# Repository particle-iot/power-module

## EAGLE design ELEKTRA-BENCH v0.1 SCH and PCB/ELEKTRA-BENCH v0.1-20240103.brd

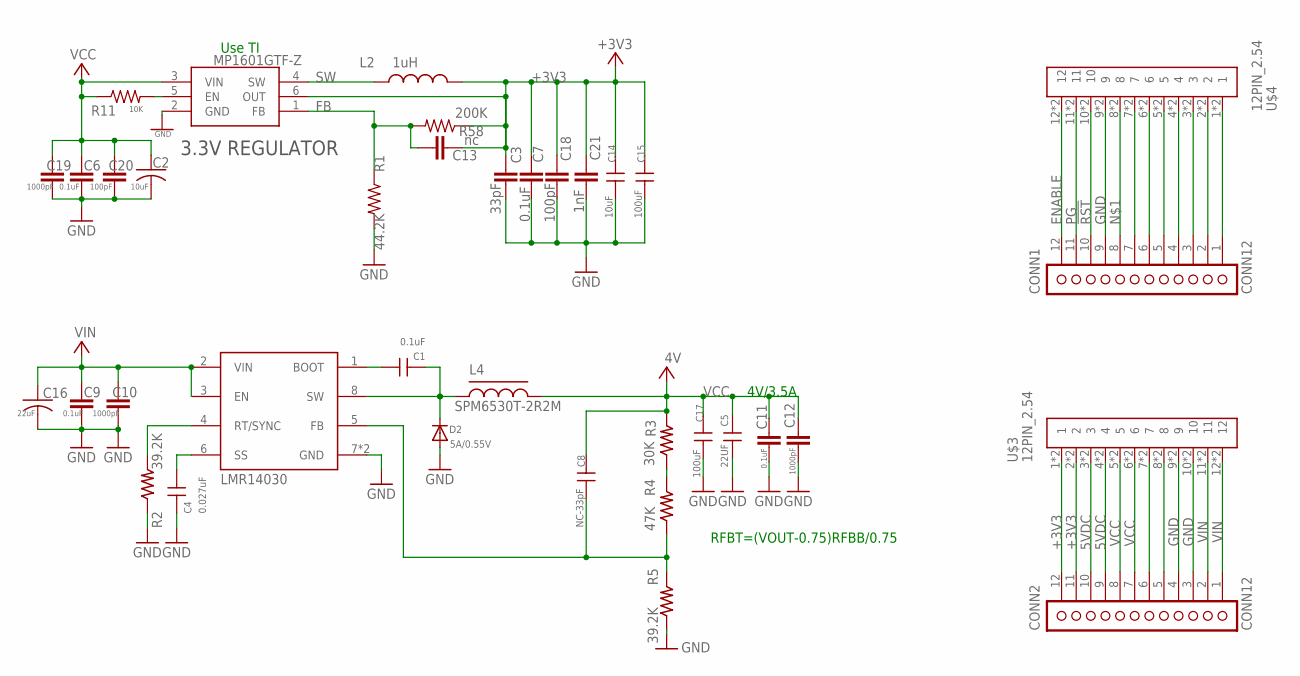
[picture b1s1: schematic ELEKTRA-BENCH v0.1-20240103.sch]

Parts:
C1: 0.1uF; C0402
C2: 10uF; C0603_B
C3: 33pF; C0402_B
C4: 0.027uF; C0402
C5: 22UF; C0805
C6, C7, C9, C11: 0.1uF; C0402_B
C8: NC-33pF; C0402
C10, C12, C19: 1000pF; C0402_B
C13: nc; C0402_B
C14: 10uF; C0805
C15, C17: 100uF; C1206
C16: 22uF; C0603_B
C18, C20: 100pF; C0402_B
C21: 1nF; C0402_B
CONN1, CONN2: CONN12; 1X12_SMD_STRAIGHT
D2: 5A/0.55V; SMADIODE
L2: 1uH; INDUCTOR-VLS-E
L4: SPM6530T-2R2M; INDCUTOR_SPM6530
R1: 44.2K; R0402_B
R2, R5: 39.2K; R-0402S
R3: 30K; R-0402S
R4: 47K; R-0402S
R11: 10K; R0402_B
R58: 200K; R0402_B
U2: LMR14030; SO_POWERPAD_8
U3: MP1601GTF-Z; SOTFL50P160X60-6N
U$3, U$4: 12PIN_2.54

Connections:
5VDC: CONN2.9, CONN2.10, U$3.3, U$3.4, U$3.P$3 (3), U$3.P$4 (4)
!RST: CONN1.10, U$4.10, U$4.P$10 (10)
+3V3: C3.2, C7.2, C13.1, C14.1, C15.1, C18.2, C21.2, CONN2.11, CONN2.12, L2.P$2 (2), R58.1, U3.6 (OUT), U$3.1, U$3.2, U$3.P$1 (1), U$3.P$2 (2)
ENABLE: CONN1.12, U$4.12, U$4.P$12 (12)
FB: C13.2, R1.1, R58.2, U3.1 (FB)
GND: C2.2, C3.1, C4.2, C5.2, C6.1, C7.1, C9.1, C10.1, C11.1, C12.1, C14.2, C15.2, C16.2, C17.2, C18.1, C19.1, C20.1, C21.1, CONN1.9, CONN2.3, CONN2.4, D2.A, R1.2, R2.1, R5.1, U2.7 (GND), U2.EP (GND), U3.2 (GND), U$3.9, U$3.10, U$3.P$9 (9), U$3.P$10 (10), U$4.9, U$4.P$9 (9)
unnamed: CONN1.8, U$4.8, U$4.P$8 (8)
unnamed: C8.1, R4.1, R5.2, U2.5 (FB)
unnamed: CONN1.7, U$4.7, U$4.P$7 (7)
unnamed: CONN1.6, U$4.6, U$4.P$6 (6)
unnamed: CONN1.5, U$4.5, U$4.P$5 (5)
unnamed: CONN1.4, U$4.4, U$4.P$4 (4)
unnamed: R11.2, U3.5 (EN)
unnamed: C4.1, U2.6 (SS)
unnamed: C1.2, D2.C, L4.1, U2.8 (SW)
unnamed: C1.1, U2.1 (BOOT)
unnamed: R2.2, U2.4 (RT/SYNC)
unnamed: R3.1, R4.2
unnamed: CONN1.3, U$4.3, U$4.P$3 (3)
unnamed: CONN1.2, U$4.2, U$4.P$2 (2)
unnamed: CONN1.1, U$4.1, U$4.P$1 (1)
unnamed: CONN2.6, U$3.7, U$3.P$7 (7)
unnamed: CONN2.5, U$3.8, U$3.P$8 (8)
PG: CONN1.11, U$4.11, U$4.P$11 (11)
SW: L2.P$1 (1), U3.4 (SW)
VCC: C2.1, C5.1, C6.2, C8.2, C11.2, C12.2, C17.1, C19.2, C20.2, CONN2.7, CONN2.8, L4.2, R3.2, R11.1, U3.3 (VIN), U$3.5, U$3.6, U$3.P$5 (5), U$3.P$6 (6)
VIN: C9.2, C10.2, C16.1, CONN2.1, CONN2.2, U2.2 (VIN), U2.3 (EN), U$3.11, U$3.12, U$3.P$11 (11), U$3.P$12 (12)

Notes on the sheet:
4V/3.5A
3.3V REGULATOR
RFBT=(VOUT-0.75)RFBB/0.75
Use TI

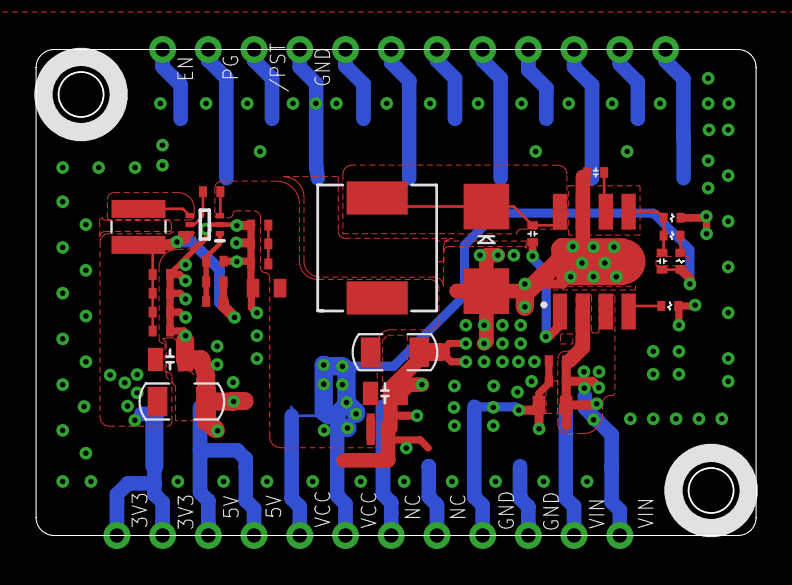
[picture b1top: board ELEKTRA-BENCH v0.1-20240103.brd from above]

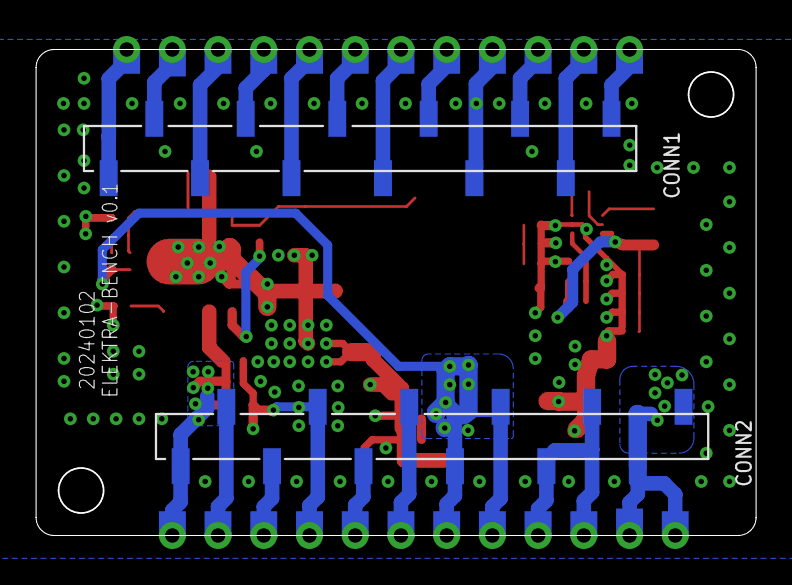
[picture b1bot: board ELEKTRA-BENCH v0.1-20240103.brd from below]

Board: 2 copper layers, 40.0 x 27.0 mm, 37 parts (2 on the bottom side), 27 nets.

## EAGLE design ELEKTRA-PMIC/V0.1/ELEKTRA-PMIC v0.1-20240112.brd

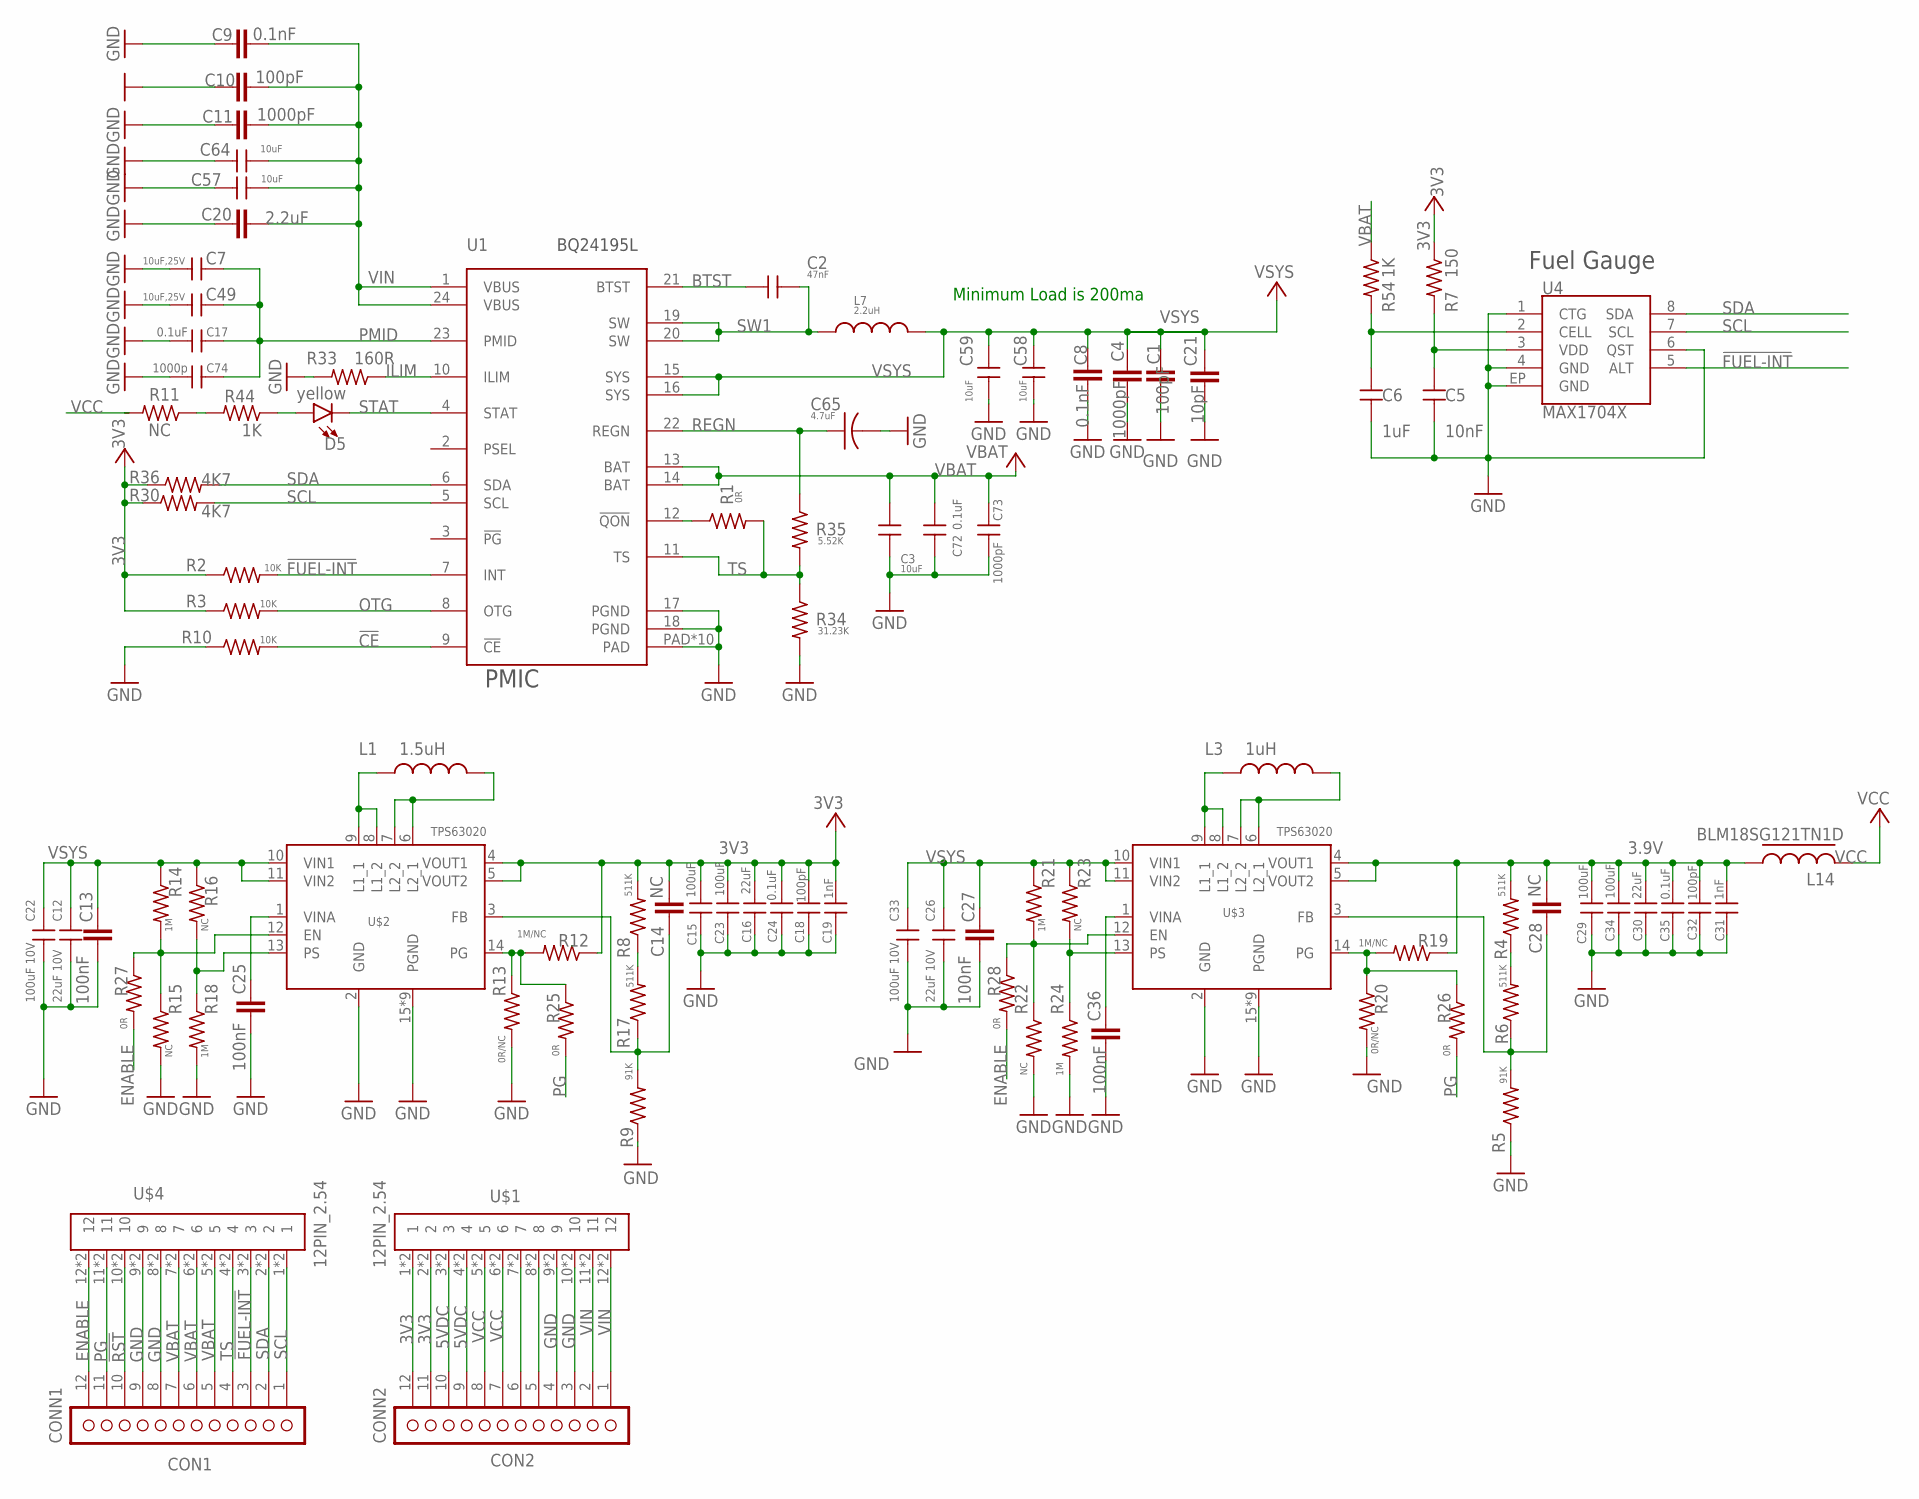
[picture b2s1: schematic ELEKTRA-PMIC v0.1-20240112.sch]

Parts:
C1, C10: 100pF; C0402_B
C2: 47nF; C-0402
C3: 10uF; C0603
C4, C11: 1000pF; C0402_B
C5: 10nF; C0402
C6: 1uF; C0402
C7, C49: 10uF,25V; C-0603A
C8, C9: 0.1nF; C0402_B
C12, C26: 22uF 10V; C0805
C13, C25, C27, C36: 100nF; C0402_B
C14, C28: NC; C0402_B
C15, C23, C29, C34: 100uF; C1206
C16, C30: 22uF; C-0603A
C17, C24, C35: 0.1uF; C0402
C18, C32: 100pF; C0402
C19, C31: 1nF; C0402
C20: 2.2uF; C0402_B
C21: 10pF; C0402_B
C22, C33: 100uF 10V; C1206
C57, C58, C59, C64: 10uF; C-0603A
C65: 4.7uF; C0603_B
C72: 0.1uF; C-0402
C73: 1000pF; C-0402
C74: 1000p; C-0402
CONN1: CON1; 1X12_SMD_STRAIGHT
CONN2: CON2; 1X12_SMD_STRAIGHT
D5: yellow; LED-0603
L1: 1.5uH; INDUCTOR-VLS-E
L3: 1uH; INDUCTOR-VLS-E
L7: 2.2uH; INDUCTOR-4040
L14: BLM18SG121TN1D; R-0603A
R1, R25, R26, R27, R28: 0R; R0402_B
R2, R3, R10: 10K; R0402_B
R4, R6, R8, R17: 511K; R0402_B
R5, R9: 91K; R0402_B
R7: 150; R0402_B
R11, R15, R16, R22, R23: NC; R0402_B
R12, R19: 1M/NC; R0402_B
R13, R20: 0R/NC; R0402_B
R14, R18, R21, R24: 1M; R0402_B
R30, R36: 4K7; R0402_B
R33: 160R; R0402_B
R34: 31.23K; R0402_B
R35: 5.52K; R0402_B
R44, R54: 1K; R0402_B
U1: BQ24195L; QFN24
U4: MAX1704X; TDFN-8
U$1, U$4: 12PIN_2.54
U$2, U$3: TPS63020

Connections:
3.9V: C28.2, C29.1, C30.1, C31.1, C32.1, C34.1, C35.1, L14.2, R4.2, R19.1, U$3.4 (VOUT1), U$3.5 (VOUT2)
3V3: C14.2, C15.1, C16.1, C18.1, C19.1, C23.1, C24.1, CONN2.11, CONN2.12, R2.1, R3.1, R7.1, R8.2, R12.1, R30.1, R36.1, U$1.1, U$1.2, U$1.P$1 (1), U$1.P$2 (2), U$2.4 (VOUT1), U$2.5 (VOUT2)
5VDC: CONN2.9, CONN2.10, U$1.3, U$1.4, U$1.P$3 (3), U$1.P$4 (4)
!CE: R10.2, U1.9 (!CE)
!FUEL-INT: CONN1.3, R2.2, U1.7 (INT), U4.5 (ALT), U$4.3, U$4.P$3 (3)
!RST: CONN1.10, U$4.10, U$4.P$10 (10)
BTST: C2.1, U1.21 (BTST)
ENABLE: CONN1.12, R27.2, R28.2, U$4.12, U$4.P$12 (12)
GND: C1.1, C3.2, C4.1, C5.2, C6.2, C7.2, C8.1, C9.1, C10.1, C11.1, C12.2, C13.1, C15.2, C16.2, C17.1, C18.2, C19.2, C20.1, C21.1, C22.2, C23.2, C24.2, C25.1, C26.2, C27.1, C29.2, C30.2, C31.2, C32.2, C33.2, C34.2, C35.2, C36.1, C49.2, C57.2, C58.2, C59.2, C64.2, C65.2, C72.2, C73.2, C74.1, CONN1.8, CONN1.9, CONN2.3, CONN2.4, R5.1, R9.1, R10.1, R13.2, R15.2, R18.2, R20.2, R22.2, R24.2, R33.2, R34.2, U1.17 (PGND), U1.18 (PGND), U1.PAD, U1.PAD@1 (PAD), U1.PAD@2 (PAD), U1.PAD@3 (PAD), U1.PAD@4 (PAD), U1.PAD@5 (PAD), U1.PAD@6 (PAD), U1.PAD@7 (PAD), U1.PAD@8 (PAD), U1.PAD@9 (PAD), U4.1 (CTG), U4.4 (GND), U4.6 (QST), U4.EP (GND), U$1.9, U$1.10, U$1.P$9 (9), U$1.P$10 (10), U$2.2 (GND), U$2.15 (PGND), U$2.16 (PGND), U$2.17 (PGND), U$2.18 (PGND), U$2.19 (PGND), U$2.20 (PGND), U$2.21 (PGND), U$2.22 (PGND), U$2.23 (PGND), U$3.2 (GND), U$3.15 (PGND), U$3.16 (PGND), U$3.17 (PGND), U$3.18 (PGND), U$3.19 (PGND), U$3.20 (PGND), U$3.21 (PGND), U$3.22 (PGND), U$3.23 (PGND), U$4.8, U$4.9, U$4.P$8 (8), U$4.P$9 (9)
ILIM: R33.1, U1.10 (ILIM)
unnamed: R1.1, U1.12 (!QON)
unnamed: R11.1, R44.2
unnamed: D5.A, R44.1
unnamed: C14.1, R9.2, R17.1, U$2.3 (FB)
unnamed: C28.1, R5.2, R6.1, U$3.3 (FB)
unnamed: CONN2.6, U$1.7, U$1.P$7 (7)
unnamed: R8.1, R17.2
unnamed: R4.1, R6.2
unnamed: CONN2.5, U$1.8, U$1.P$8 (8)
unnamed: L3.P$1 (1), U$3.8 (L1_2), U$3.9 (L1_1)
unnamed: L1.P$1 (1), U$2.8 (L1_2), U$2.9 (L1_1)
unnamed: R12.2, R13.1, R25.1, U$2.14 (PG)
unnamed: R14.2, R15.1, R27.1, U$2.12 (EN)
unnamed: R16.2, R18.1, U$2.13 (PS)
unnamed: L3.P$2 (2), U$3.6 (L2_1), U$3.7 (L2_2)
unnamed: L1.P$2 (2), U$2.6 (L2_1), U$2.7 (L2_2)
unnamed: C25.2, U$2.1 (VINA)
unnamed: C36.2, U$3.1 (VINA)
unnamed: R19.2, R20.1, R26.1, U$3.14 (PG)
unnamed: R21.2, R22.1, R28.1, U$3.12 (EN)
unnamed: R23.2, R24.1, U$3.13 (PS)
unnamed: C5.1, R7.2, U4.3 (VDD)
unnamed: C6.1, R54.2, U4.2 (CELL)
OTG: R3.2, U1.8 (OTG)
PG: CONN1.11, R25.2, R26.2, U$4.11, U$4.P$11 (11)
PMID: C7.1, C17.2, C49.1, C74.2, U1.23 (PMID)
REGN: C65.1, R35.1, U1.22 (REGN)
SCL: CONN1.1, R30.2, U1.5 (SCL), U4.7 (SCL), U$4.1, U$4.P$1 (1)
SDA: CONN1.2, R36.2, U1.6 (SDA), U4.8 (SDA), U$4.2, U$4.P$2 (2)
STAT: D5.C, U1.4 (STAT)
SW1: C2.2, L7.P$1 (1), U1.19 (SW), U1.20 (SW)
TS: CONN1.4, R1.2, R34.1, R35.2, U1.11 (TS), U$4.4, U$4.P$4 (4)
VBAT: C3.1, C72.1, C73.1, CONN1.5, CONN1.6, CONN1.7, R54.1, U1.13 (BAT), U1.14 (BAT), U$4.5, U$4.6, U$4.7, U$4.P$5 (5), U$4.P$6 (6), U$4.P$7 (7)
VCC: CONN2.7, CONN2.8, L14.1, R11.2, U$1.5, U$1.6, U$1.P$5 (5), U$1.P$6 (6)
VIN: C9.2, C10.2, C11.2, C20.2, C57.1, C64.1, CONN2.1, CONN2.2, U1.1 (VBUS), U1.24 (VBUS), U$1.11, U$1.12, U$1.P$11 (11), U$1.P$12 (12)
VSYS: C1.2, C4.2, C8.2, C12.1, C13.2, C21.2, C22.1, C26.1, C27.2, C33.1, C58.1, C59.1, L7.P$2 (2), R14.1, R16.1, R21.1, R23.1, U1.15 (SYS), U1.16 (SYS), U$2.10 (VIN1), U$2.11 (VIN2), U$3.10 (VIN1), U$3.11 (VIN2)

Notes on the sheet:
Minimum Load is 200ma
PMIC
Fuel Gauge

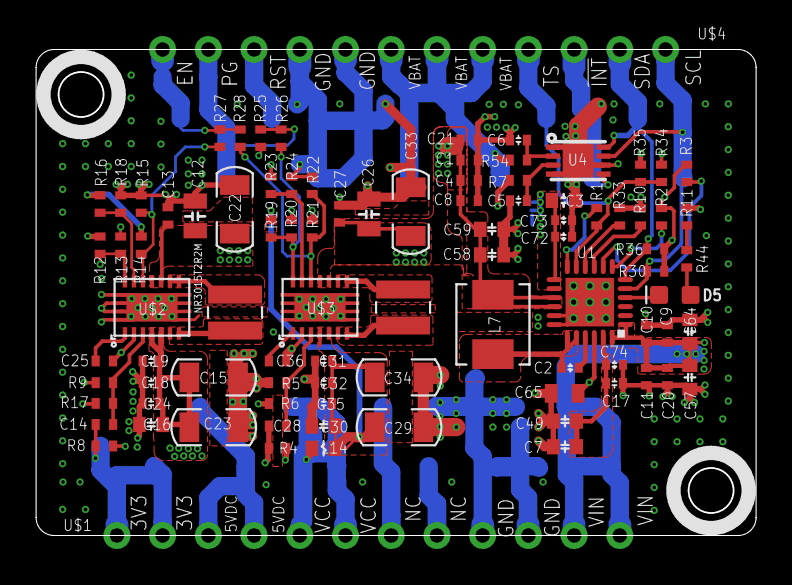
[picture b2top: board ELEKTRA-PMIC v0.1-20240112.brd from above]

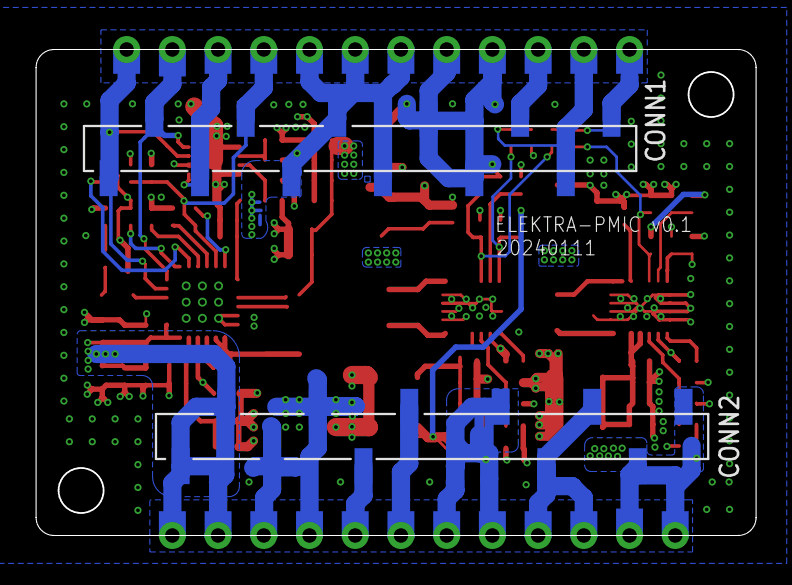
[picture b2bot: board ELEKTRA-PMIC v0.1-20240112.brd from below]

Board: 4 copper layers, 40.0 x 27.0 mm, 93 parts (2 on the bottom side), 46 nets.

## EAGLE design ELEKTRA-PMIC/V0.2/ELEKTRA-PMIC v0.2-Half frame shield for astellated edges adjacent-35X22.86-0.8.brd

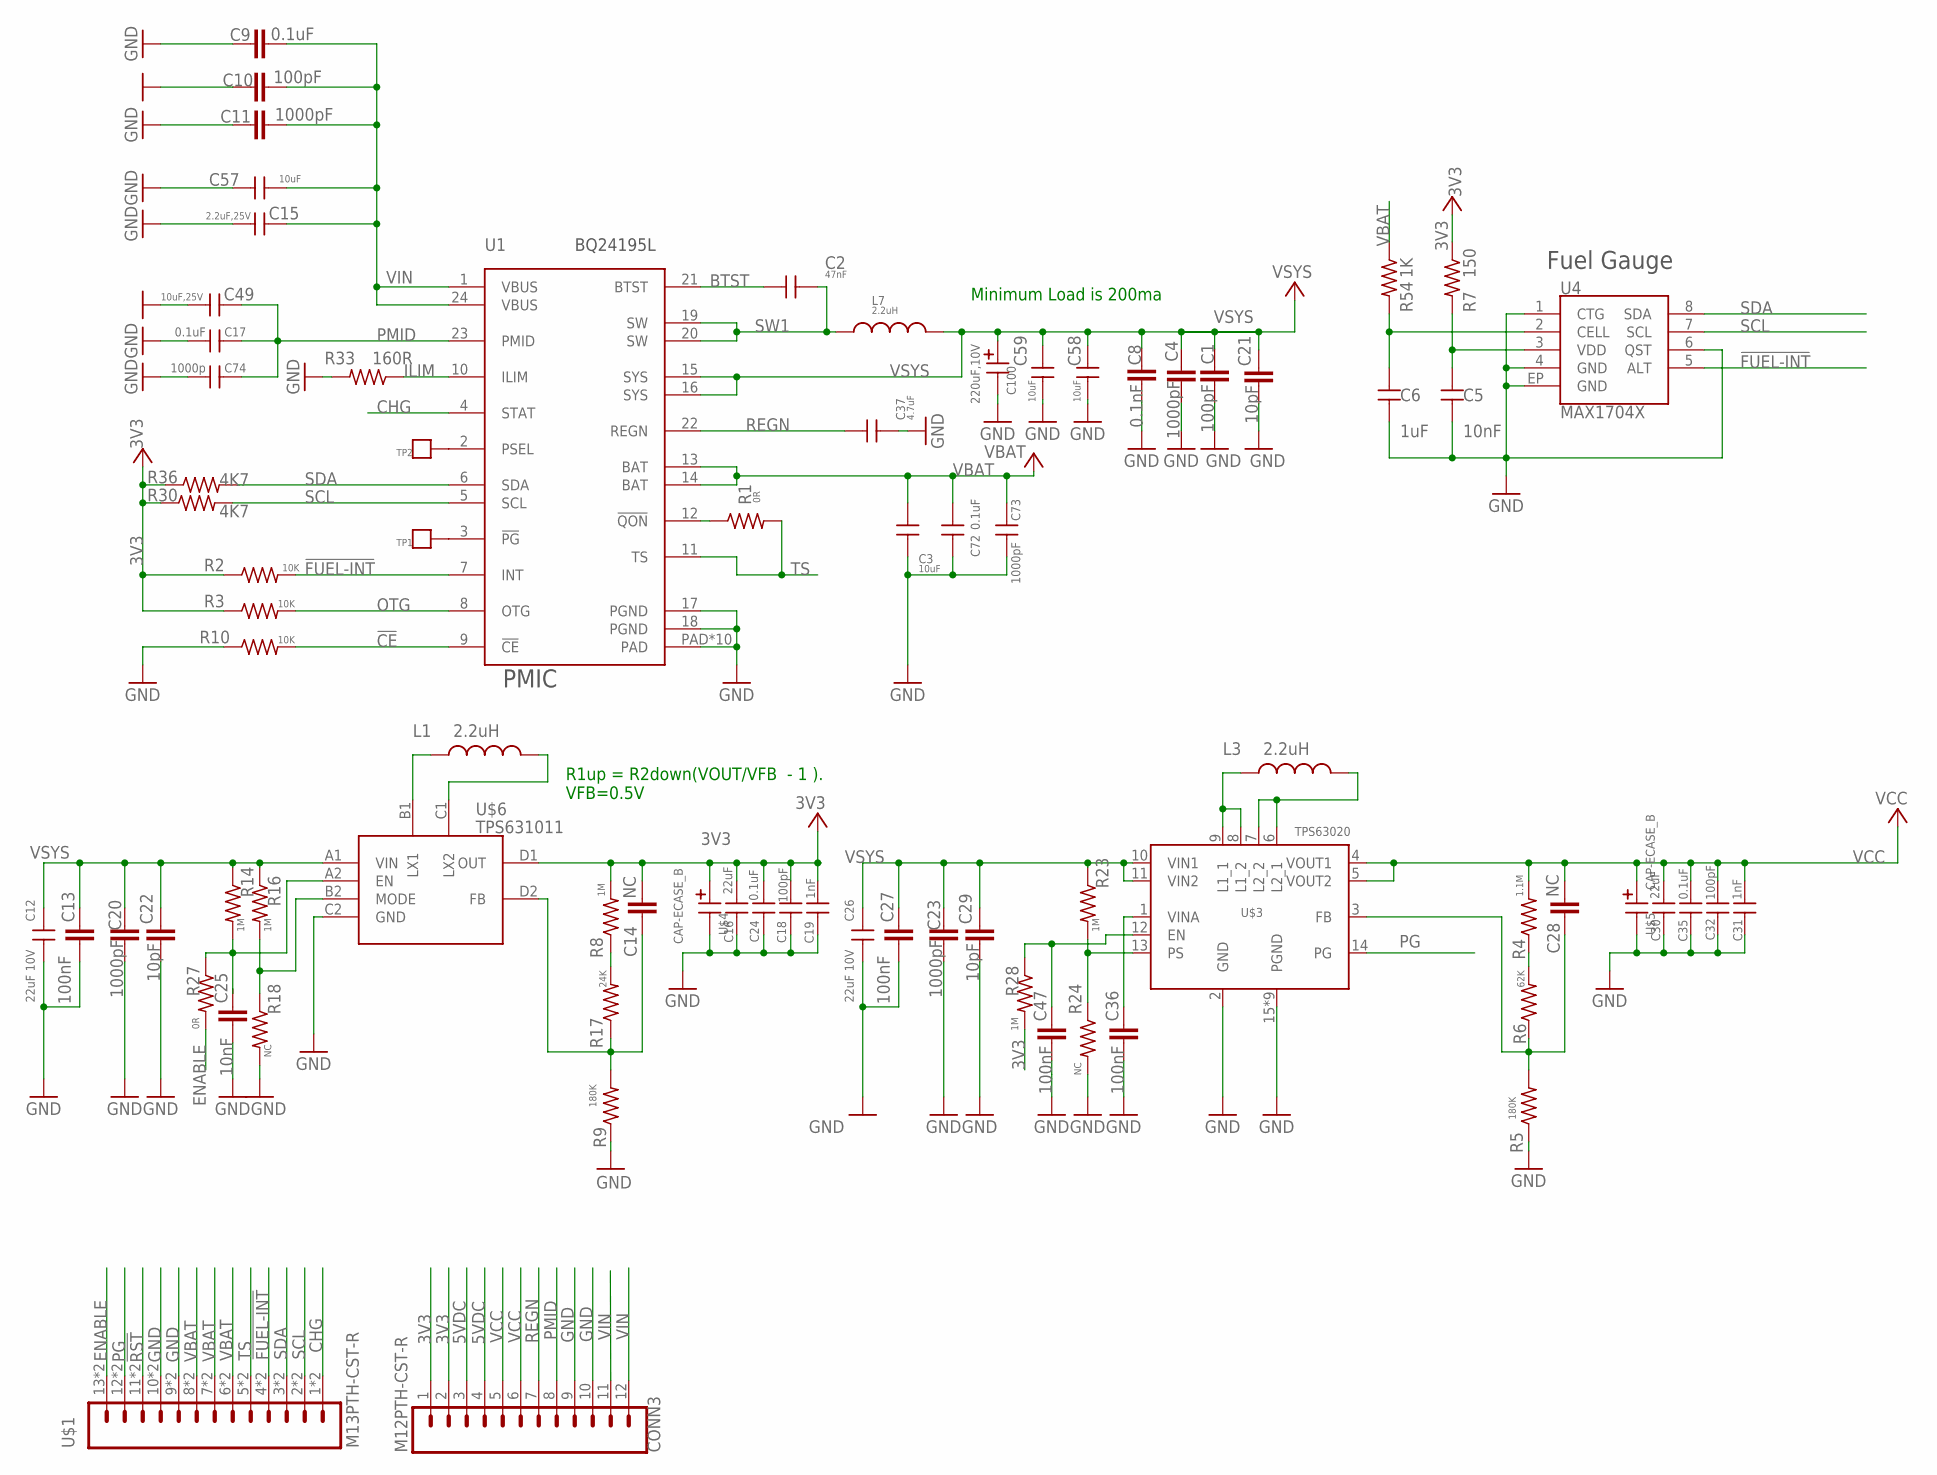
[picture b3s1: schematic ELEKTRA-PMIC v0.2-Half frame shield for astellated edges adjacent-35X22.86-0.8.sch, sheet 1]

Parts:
C1, C10: 100pF; C0402_B
C2: 47nF; C-0402
C3: 10uF; C0603
C4, C11, C20, C23: 1000pF; C0402_B
C5: 10nF; C0402
C6: 1uF; C0402
C8: 0.1nF; C0402_B
C9: 0.1uF; C0402_B
C12, C26: 22uF 10V; C0805
C13, C27, C36, C47: 100nF; C0402_B
C14, C28: NC; C0402_B
C15: 2.2uF,25V; C-0603A
C16, C30: 22uF; C-0603A
C17, C24, C35: 0.1uF; C0402
C18, C32: 100pF; C0402
C19, C31: 1nF; C0402
C21, C22, C29: 10pF; C0402_B
C25: 10nF; C0402_B
C37: 4.7uF; C0402
C49: 10uF,25V; C-0603A
C57, C58, C59: 10uF; C-0603A
C72: 0.1uF; C-0402
C73: 1000pF; C-0402
C74: 1000p; C-0402
C100: 220uF,10V; CASE-B
CONN3: M12PTH-CST-R; 1X12-CASTELLATED
L1, L3: 2.2uH; INDUCTOR-VLS-E
L7: 2.2uH; INDUCTOR-4040
R1, R27: 0R; R0402_B
R2, R3, R10: 10K; R0402_B
R4: 1.1M; R0402_B
R5, R9: 180K; R0402_B
R6: 62K; R0402_B
R7: 150; R0402_B
R8, R14, R16, R23, R28: 1M; R0402_B
R17: 24K; R0402_B
R18, R24: NC; R0402_B
R30, R36: 4K7; R0402_B
R33: 160R; R0402_B
R54: 1K; R0402_B
TP1, TP2: TP; TP0.7MM
U1: BQ24195L; QFN24
U4: MAX1704X; TDFN-8
U$1: M13PTH-CST-R; 1X13-CASTELLATED
U$3: TPS63020
U$4, U$5: CAP-ECASE_B; CASE-B
U$6: TPS631011; DSBGA

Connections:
3V3: C14.2, C16.1, C18.1, C19.1, C24.1, CONN3.1, CONN3.2, R2.1, R3.1, R7.1, R8.2, R28.2, R30.1, R36.1, U$4.P$1 (1), U$6.D1 (OUT)
5VDC: CONN3.3, CONN3.4
!CE: R10.2, U1.9 (!CE)
!FUEL-INT: R2.2, U1.7 (INT), U4.5 (ALT), U$1.4, U$1.@4 (4)
!RST: U$1.11, U$1.@11 (11)
BTST: C2.1, U1.21 (BTST)
CHG: U1.4 (STAT), U$1.1, U$1.@1 (1)
ENABLE: R27.2, U$1.13, U$1.@13 (13)
GND: C1.1, C3.2, C4.1, C5.2, C6.2, C8.1, C9.1, C10.1, C11.1, C12.2, C13.1, C15.2, C16.2, C17.1, C18.2, C19.2, C20.1, C21.1, C22.1, C23.1, C24.2, C25.1, C26.2, C27.1, C29.1, C30.2, C31.2, C32.2, C35.2, C36.1, C37.2, C47.1, C49.2, C57.2, C58.2, C59.2, C72.2, C73.2, C74.1, C100.P$2 (2), CONN3.9, CONN3.10, R5.1, R9.1, R10.1, R18.2, R24.2, R33.2, U1.17 (PGND), U1.18 (PGND), U1.PAD, U1.PAD@1 (PAD), U1.PAD@2 (PAD), U1.PAD@3 (PAD), U1.PAD@4 (PAD), U1.PAD@5 (PAD), U1.PAD@6 (PAD), U1.PAD@7 (PAD), U1.PAD@8 (PAD), U1.PAD@9 (PAD), U4.1 (CTG), U4.4 (GND), U4.6 (QST), U4.EP (GND), U$1.9, U$1.10, U$1.@9 (9), U$1.@10 (10), U$3.2 (GND), U$3.15 (PGND), U$3.16 (PGND), U$3.17 (PGND), U$3.18 (PGND), U$3.19 (PGND), U$3.20 (PGND), U$3.21 (PGND), U$3.22 (PGND), U$3.23 (PGND), U$4.P$2 (2), U$5.P$2 (2), U$6.C2 (GND)
ILIM: R33.1, U1.10 (ILIM)
unnamed: R1.1, U1.12 (!QON)
unnamed: TP1.P$1, U1.3 (!PG)
unnamed: C14.1, R9.2, R17.1, U$6.D2 (FB)
unnamed: C28.1, R5.2, R6.1, U$3.3 (FB)
unnamed: TP2.P$1, U1.2 (PSEL)
unnamed: R8.1, R17.2
unnamed: R4.1, R6.2
unnamed: L3.P$1 (1), U$3.8 (L1_2), U$3.9 (L1_1)
unnamed: L1.P$1 (1), U$6.B1 (LX1)
unnamed: C25.2, R14.2, R27.1, U$6.A2 (EN)
unnamed: R16.2, R18.1, U$6.B2 (MODE)
unnamed: L3.P$2 (2), U$3.6 (L2_1), U$3.7 (L2_2)
unnamed: L1.P$2 (2), U$6.C1 (LX2)
unnamed: C36.2, U$3.1 (VINA)
unnamed: C47.2, R28.1, U$3.12 (EN)
unnamed: R23.2, R24.1, U$3.13 (PS)
unnamed: C5.1, R7.2, U4.3 (VDD)
unnamed: C6.1, R54.2, U4.2 (CELL)
OTG: R3.2, U1.8 (OTG)
PG: U$1.12, U$1.@12 (12), U$3.14 (PG)
PMID: C17.2, C49.1, C74.2, CONN3.8, U1.23 (PMID)
REGN: C37.1, CONN3.7, U1.22 (REGN)
SCL: R30.2, U1.5 (SCL), U4.7 (SCL), U$1.2, U$1.@2 (2)
SDA: R36.2, U1.6 (SDA), U4.8 (SDA), U$1.3, U$1.@3 (3)
SW1: C2.2, L7.P$1 (1), U1.19 (SW), U1.20 (SW)
TS: R1.2, U1.11 (TS), U$1.5, U$1.@5 (5)
VBAT: C3.1, C72.1, C73.1, R54.1, U1.13 (BAT), U1.14 (BAT), U$1.6, U$1.7, U$1.8, U$1.@6 (6), U$1.@7 (7), U$1.@8 (8)
VCC: C28.2, C30.1, C31.1, C32.1, C35.1, CONN3.5, CONN3.6, R4.2, U$3.4 (VOUT1), U$3.5 (VOUT2), U$5.P$1 (1)
VIN: C9.2, C10.2, C11.2, C15.1, C57.1, CONN3.11, CONN3.12, U1.1 (VBUS), U1.24 (VBUS)
VSYS: C1.2, C4.2, C8.2, C12.1, C13.2, C20.2, C21.2, C22.2, C23.2, C26.1, C27.2, C29.2, C58.1, C59.1, C100.P$1 (1), L7.P$2 (2), R14.1, R16.1, R23.1, U1.15 (SYS), U1.16 (SYS), U$3.10 (VIN1), U$3.11 (VIN2), U$6.A1 (VIN)

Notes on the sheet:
Minimum Load is 200ma
PMIC
Fuel Gauge
R1up = R2down(VOUT/VFB - 1 ). VFB=0.5V

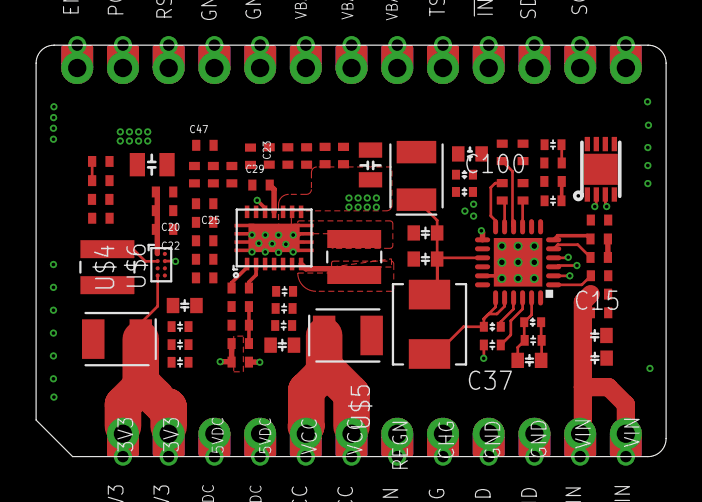
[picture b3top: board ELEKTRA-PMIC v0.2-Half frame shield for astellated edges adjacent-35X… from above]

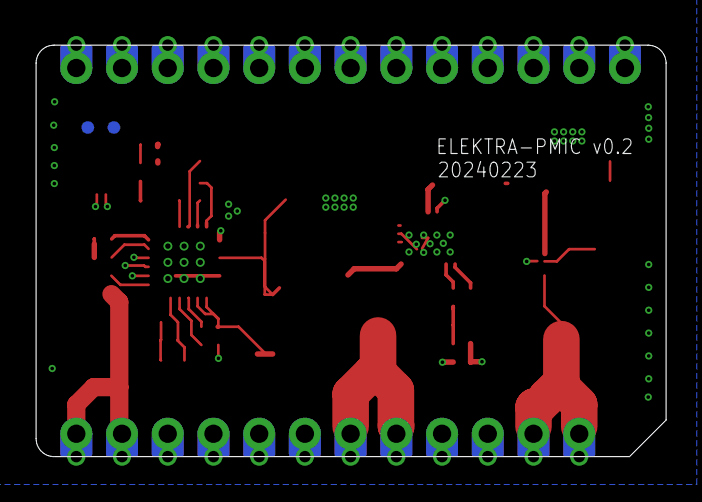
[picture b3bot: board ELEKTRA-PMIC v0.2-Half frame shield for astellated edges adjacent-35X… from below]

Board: 4 copper layers, 35.0 x 22.9 mm, 78 parts (2 on the bottom side), 40 nets.

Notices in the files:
parts and their libraries:
SparkFun-LED: Licensing: Creative Commons ShareAlike 4.0 International - https://creativecommons.org/licenses/by-sa/4.0
